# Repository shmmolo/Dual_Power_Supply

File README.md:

# Dual Power Supply Board

Compact ±12 V dual linear regulated power supply using LM317 and LM337 regulators.  
Designed for analog circuits, op-amp testing, and audio applications.

## Features
- 230 VAC input via Hammond 162J24 (12-0-12 V @ 1.5 A)
- Full-bridge rectifier (KBPC6)
- 22 000 µF filtering capacitors
- Adjustable ±1.25 V → ±12 V outputs
- Overcurrent & reverse-polarity protection

## Components
- **TR1:** Hammond 162J24 Transformer  
- **D1:** KBPC6 Bridge Rectifier  
- **U1 / U2:** LM317T, LM337T Regulators  
- **C1–C10:** Filtering and decoupling capacitors  
- **RV1 / RV2:** Adjustment potentiometers  
- **D2–D7:** Protection diodes  
- **J2:** Phoenix 3-pin Output Terminal

## Output Range
| Rail | Voltage | Current |
|------|----------|----------|
| V+   | +1.25 → +12 V | up to 1.5 A |
| V–   | –1.25 → –12 V | up to 1.5 A |

## Applications
- Audio preamp and op-amp circuits  
- Dual-supply analog prototypes  
- Lab power supply for small projects

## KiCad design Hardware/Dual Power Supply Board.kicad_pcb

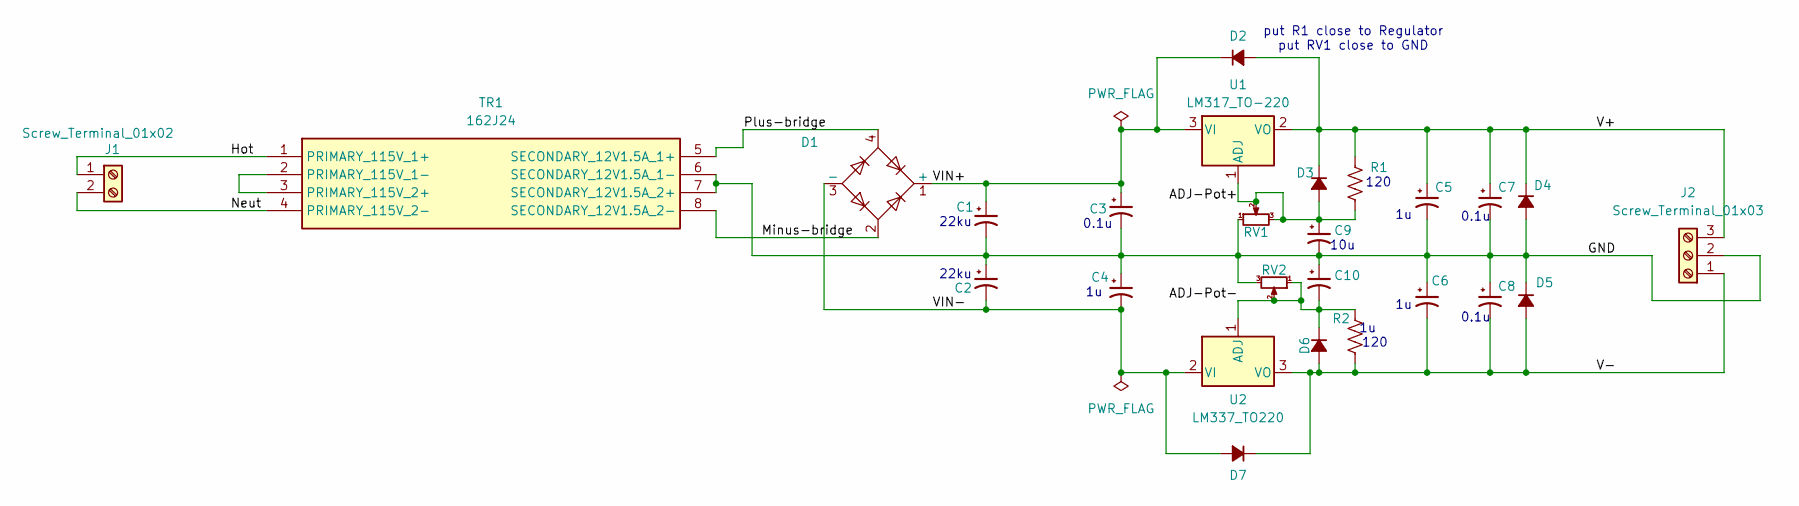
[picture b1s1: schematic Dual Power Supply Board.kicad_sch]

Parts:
C1, C2: 22ku; CP_Radial_D5.0mm_P2.50mm
C3, C7, C8: 0.1u; C_Disc_D3.4mm_W2.1mm_P2.50mm
C4, C5, C6: 1u; C_Disc_D3.4mm_W2.1mm_P2.50mm
C9, C10: C_Polarized_Small_US; CP_Radial_D5.0mm_P2.50mm
D1: Diode_Bridge_Vishay_KBPC6
D2, D3, D6, D7: D_Small_Filled; D_DO-41_SOD81_P7.62mm_Horizontal
D4, D5: D_DO-41_SOD81_P7.62mm_Horizontal
J1: Screw_Terminal_01x02; TerminalBlock_Phoenix_MKDS-1,5-2-5.08_1x02_P5.08mm_Horizont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
J2: Screw_Terminal_01x03; TerminalBlock_Phoenix_MKDS-1,5-3-5.08_1x03_P5.08mm_Horizont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
R1, R2: R_US; R_Axial_DIN0207_L6.3mm_D2.5mm_P7.62mm_Horizontal
RV1, RV2: R_Potentiometer_Small; Potentiometer_Bourns_3266W_Vertical
TR1: 162J24; Manufacturer_Part_Number 162J24; Mouser Part Number 546-162J24
U1: LM317_TO-220; TO-220-3_Vertical
U2: LM337_TO220; TO-220-3_Vertical

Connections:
/ADJ-Pot+: C9.1, D3.2 (A), R1.2, RV1.2, RV1.3, U1.1 (ADJ)
/ADJ-Pot-: C10.2, D6.1 (K), R2.2, RV2.1, RV2.2, U2.1 (ADJ)
/GND: C1.2, C2.1, C3.2, C4.1, C5.2, C6.1, C7.2, C8.1, C9.2, C10.1, D4.2 (A), D5.1 (K), J2.2, RV1.1, RV2.3, TR1.6 (SECONDARY_12V1.5A_1-), TR1.7 (SECONDARY_12V1.5A_2+)
/Hot: J1.1, TR1.1 (PRIMARY_115V_1+)
/Minus-bridge: D1.2, TR1.8 (SECONDARY_12V1.5A_2-)
/Neut: J1.2, TR1.4 (PRIMARY_115V_2-)
/Plus-bridge: D1.4, TR1.5 (SECONDARY_12V1.5A_1+)
/V+: C5.1, C7.1, D2.2 (A), D3.1 (K), D4.1 (K), J2.3, R1.1, U1.2 (VO)
/V-: C6.2, C8.2, D5.2 (A), D6.2 (A), D7.1 (K), J2.1, R2.1, U2.3 (VO)
/VIN+: C1.1, C3.1, D1.1 (+), D2.1 (K), U1.3 (VI)
/VIN-: C2.2, C4.2, D1.3 (-), D7.2 (A), U2.2 (VI)
unnamed: TR1.2 (PRIMARY_115V_1-), TR1.3 (PRIMARY_115V_2+)

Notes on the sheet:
0.1u
120
22ku
put R1 close to Regulator put RV1 close to GND
120
10u

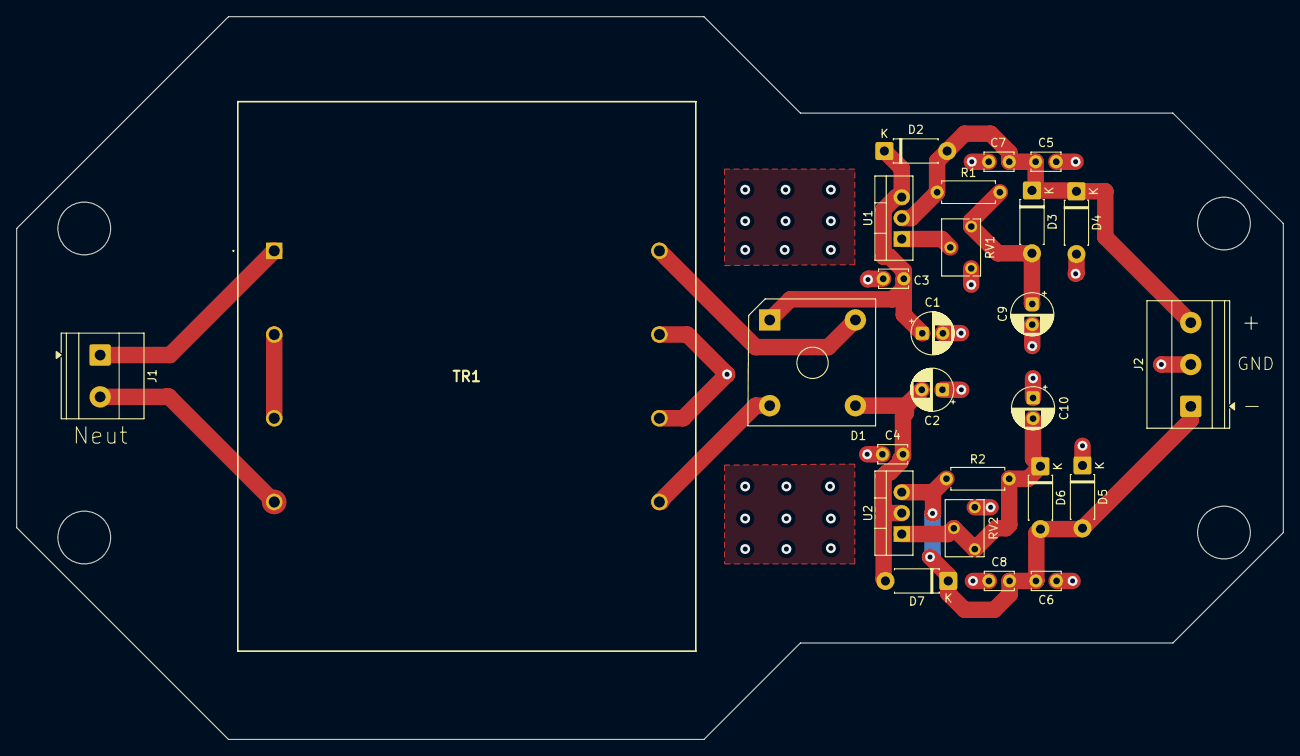
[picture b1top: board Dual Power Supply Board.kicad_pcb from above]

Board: 2 copper layers, 153.7 x 87.7 mm, 26 parts (0 on the bottom side), 12 nets.

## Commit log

2025-10-29 README.md
2025-10-29 Added to Hardware
2025-10-29 Added to Docs
